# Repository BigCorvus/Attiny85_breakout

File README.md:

# Attiny85_breakout
This tiny Attiny85 breakout board comes in handy in many small projects. It's programmed via ICSP. No need for bootloader hassle.See http://www.thinkering.de/cms/?p=677

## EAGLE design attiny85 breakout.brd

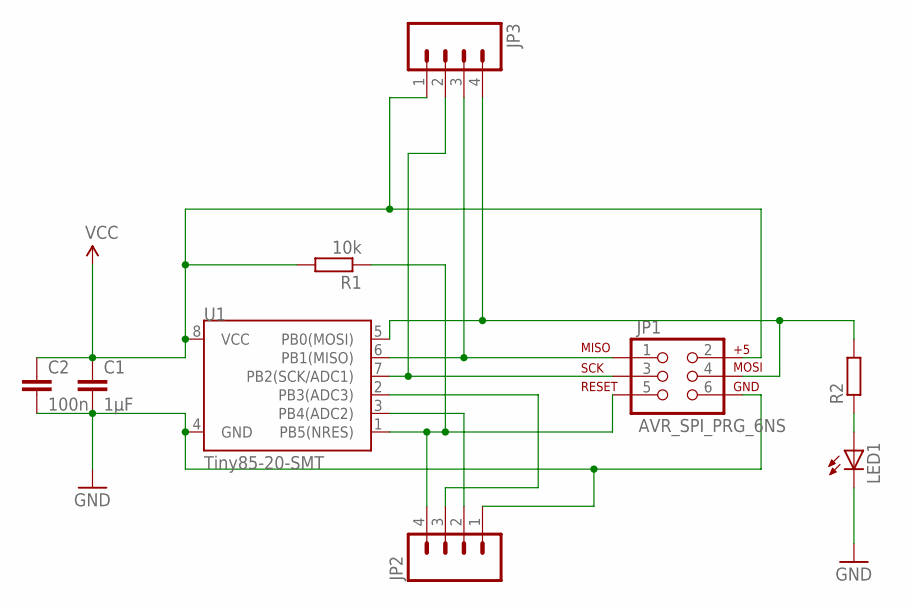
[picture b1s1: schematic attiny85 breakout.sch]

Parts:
C1: 1µF; C0805
C2: 100n; C0805
JP1: AVR_SPI_PRG_6NS; 2X3-NS
JP2, JP3: M04PTH; 1X04
LED1: LEDCHIPLED_0805; CHIPLED_0805
R1: 10k; R0805
R2: R-EU_R0603; R0603
U1: Tiny85-20-SMT; SO08-EIAJ

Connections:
GND: C1.2, C2.2, JP1.6, JP2.1, LED1.C, U1.4 (GND)
unnamed: LED1.A, R2.1
unnamed: JP1.5, JP2.4, R1.1, U1.1 (PB5(NRES))
unnamed: JP1.1, JP3.3, U1.6 (PB1(MISO))
unnamed: JP1.4, JP3.4, R2.2, U1.5 (PB0(MOSI))
unnamed: JP1.3, JP3.2, U1.7 (PB2(SCK/ADC1))
unnamed: JP2.3, U1.2 (PB3(ADC3))
unnamed: JP2.2, U1.3 (PB4(ADC2))
VCC: C1.1, C2.1, JP1.2, JP3.1, R1.2, U1.8 (VCC)

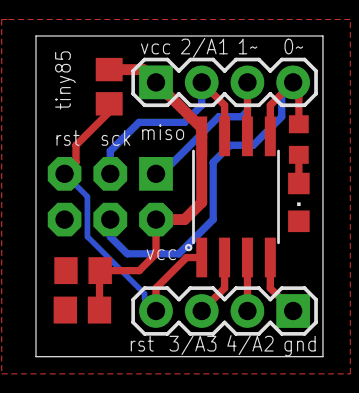
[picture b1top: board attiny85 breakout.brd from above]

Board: 2 copper layers, 15.9 x 17.8 mm, 9 parts (0 on the bottom side), 9 nets.

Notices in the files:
parts and their libraries:
SparkFun-Connectors: Licensing: Creative Commons ShareAlike 4.0 International - https://creativecommons.org/licenses/by-sa/4.0
